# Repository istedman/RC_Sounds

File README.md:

# RC Sounds
A simple, low cost sound effect module for R/C vehicles, land or water based. It utilises a DF Robot DFR0299 MP3 module to continuously play a selected MP3 sound file. A Microchip ATTiny85 provides MP3 control functions, error handling and can support two servo PWM inputs. A set of 4 switches are used to provide easy selection of the desired sound sample. Using one of the PWM inputs, a horn/siren sound can be overlaid and once it finishes playing, normal sound resume. The horn/siren setting is programmable to allow for different receiver outputs.

A PAM8403 Class D amplifier, with EMC fixes is also provided, this allows the system to drive 2x 8 ohm speakers at 2W. Volume control is provided on-board as well as an option to mute the amplifier and finally use an external amplifier, if desired using the pre-amp outputs.

PCB designed to fit into a Hammond 1594B enclosure.

Total cost of all parts, PCB, enclosure and speakers is approximately £30. See the BOM directory for an HTML export with full ordering part numbers.

## Current state as of 25th June 2025.
Design is working well. Has based compatibility tests with multiple AM/2.4 GHz receivers, 2-6 channels and has been field tested.

Use the updated V1.2_1_int software, this adds 4 speeds to the engine sounds and utilises the auxilary input to act as the throttle. The software is written in the Arduino IDE, it uses the ATtinyCore library and no bootloader. The board must be programmed using a progammer, I use a USBASP. To allow the PWM settings function to work, you have to disable the reset function on the fuses. A high voltage programmer is required to unlock. I use this design, https://github.com/wokwi/attiny-hvsp-programmer and clip onto the ATTiny85. All fuse setting defined in the software.

ATTiny85 fuse settings are in the header of the main source code, use USBASP/Avrdudess to set them.

## Boat sound effects SD card image now available

My example SD card image, for boats has now been uploaded to the repository.

## Powering the design

Power is from a 3.7-12V supply or the receiver BEC circuit. Unit has a polyfuse to protect against reverse polarity and a linear regulator.
Do not use with a 1S LiPO ESC or any other ESC that boosts the BEC output. The current design assumes the stndard +5V BEC output voltage. My 1S LiPO ESCs output
6 or 7.2V to boost the servo power, using such an ESC (Trackstar Gen II 120A or Hobbywing Xerun) would irreprably damage the design as it will operate with 5.5V maximum.

You will need an UltraBEC/SuperBEC ESC, i.e. one that can output 2A @ 5V for reliable operation. This unit can demand a peak 0.6A @ 5V, when tested with a 1A BEC, and 3-4 servos, I had a few brownouts. If it reandomly resets at the same time as your receiver, use the external power option and remove the BEC jumper!

## Schematic and circuit description

Power comes from the 5V BEC output of the ESC, if you fit a jumper on J7 of from a 3.7-12V source via J2, using appropriate wire. Connections via J2 have a 1.1A polyfuse and a LD29080-5 5V, 800mA LDO regulator, which provde revers polarity protection.

The ATTiny 85 microcontroller provides the control function. It reads the PWM inputs from two receiver channels, the horn/hooter input connects to pin 5 and the throttle input connects to pin 6. 

Communications to/from the DFR0299 MP3 module are via pins 2 & 3 and use a standard 9600 8N1 serial interface. A USB to TTL adaptor can be connected to the TX output of the ATTiny 85 on pin 2 for debug messages, using J3.

A solitary LED, D1 is used to setup functions and when the horn has been activated.

A set of DIP switches, SW1, set various analogue voltages that determine the sound sample to be played. Limits are defined in the software. A setup switch, S1 is used in the setup routine to set the horn on/off position and the throttle positions.

The DAC output of the DFR0299 is connected, via a dual gang audio potentiometer R17A/B to a PAM8403 audio amplifier. J6 provides a pre-amplifier output.
The DFR0299 DAC outputs, post volume control are AC coupled via C2 and C3. Connector J1 can be used to mute the amplifier. Capacitor C10, a 47uF capacitor, is to reduce the effects of the amplifier on the power supplies. I have added the recommended filter circuit to the output stage, using FB1-FB4 and C12-C15, this reduces radio emissions in the region of 25-40 MHz, important for RC usage as there are still some 27 and 40 MHz systems around.

Into 8 ohm speakers the design can deliver 1.8W. Peak power i've observed has been close to 2W.

A photo of the PCB

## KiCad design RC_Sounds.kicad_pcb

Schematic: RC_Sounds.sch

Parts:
C1, C8, C17: 100nF; C_0603_HandSoldering
C2, C3: 470nF; C_0603_HandSoldering
C4, C16: 10uF; CP_Tantalum_Case-B_EIA-3528-21_Hand
C5, C7: SPO; C_0603_HandSoldering
C6, C9: 1uF; C_0805_HandSoldering
C10: 470uF; CP_Tantalum_Case-E_EIA-7260-38_Hand
C11: 1uF; CP_Tantalum_Case-A_EIA-3216-18_Hand
C12, C13, C15: 220pF; C_0603_HandSoldering
C14: 220pf; C_0603_HandSoldering
D1: LED-GREEN0603; LED-0603
F1: Polyfuse_Small; Fuse_SMD1206_HandSoldering
FB1, FB2, FB3, FB4: Ferrite_Bead_Small; R_0805
H1, H2, H3, H4: STAND-OFFTIGHT; STAND-OFF-TIGHT
J1, J7: CONN_02; 1X02
J2: AVR_SPI_PROG_3X2PTH; 2X3
J3: CONN_03; 1X03
J4: CONN_02; SCREWTERMINAL-3.5MM-2
J5: CONN_04; SCREWTERMINAL-3.5MM-4
J6: CONN_04; 1X04
M1, M2: Motor_Servo_JR; 1X03
R1, R2, R5, R7, R8, R12: 10K; R_0603_HandSoldering
R3, R4: 0; R_0603_HandSoldering
R6: 2.2K; R_0603_HandSoldering
R9: 100K; R_0603_HandSoldering
R10: 47K; R_0603_HandSoldering
R11: 22K; R_0603_HandSoldering
R13: 4.7K; R_0603_HandSoldering
R14, R15: 1K; R_0603_HandSoldering
R16: 470; R_0603_HandSoldering
R17: PTV112
S1: MOMENTARY-SWITCH; TACTILE_SWITCH_SMD_5.2MM
SW1: SW_DIP_x04; DIPSWITCH-04-SMD
U1: LD29080DTR50; TO-252-2
U2: ATtiny85-20SU; SOIC-8-N
U3: PAM8403DR; SO-16-N
U4: DFR0299; MODULE_DFR0299

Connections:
+5V: C4.1, C8.1, C9.1, C10.1, C11.1, C16.1, C17.1, J2.2, J7.1, R5.1, R7.1, R8.1, R16.2, U1.3 (VO), U2.8, U3.4, U3.6, U3.13, U4.1
/LEFT+: C15.1, FB3.2, J5.1
/LEFT-: C14.1, FB1.2, J5.2
/L_AUDIO: C2.1, J6.1, R17.2.2
/RIGHT+: C12.1, FB2.2, J5.4
/RIGHT-: C13.1, FB4.2, J5.3
/RX_MICRO: J3.2, R15.1, U2.3
/R_AUDIO: C3.1, J6.4, R17.1.2
/SW_RX: R14.1, U4.2
/SW_TX: R15.2, U4.3
/TX_MICRO: J3.3, R14.2, U2.2
GND: C1.2, C4.2, C5.2, C6.2, C7.2, C8.2, C9.2, C10.2, C11.2, C12.2, C13.2, C14.2, C15.2, C16.2, C17.2, J1.1, J2.6, J3.1, J4.1, J6.2, J6.3, M1.3 (-), M2.3 (-), R9.2, R17.1.1, R17.2.1, S1.1, SW1.1, SW1.2, SW1.3, SW1.4, U1.2 (GND), U2.4, U3.2, U3.11, U3.15, U4.7, U4.10
unnamed: C1.1, F1.2, U1.1 (VI)
unnamed: C2.2, R1.1
unnamed: C3.2, R2.1
unnamed: C5.1, J2.4, R3.1, U2.5
unnamed: C6.1, U3.8
unnamed: C7.1, J2.1, R4.1, U2.6
unnamed: D1.A, R16.1
unnamed: D1.C, J2.3, U2.7
unnamed: F1.1, J4.2
unnamed: FB1.1, U3.3
unnamed: FB2.1, U3.16
unnamed: FB3.1, U3.1
unnamed: FB4.1, U3.14
unnamed: J1.2, R7.2, U3.12
unnamed: J2.5, R6.1, R8.2, R9.1, R10.1, R11.1, R12.1, R13.1, U2.1
unnamed: J7.2, M1.2 (+)
unnamed: M1.1 (PWM), R3.2
unnamed: M2.1 (PWM), R4.2
unnamed: R1.2, U3.7
unnamed: R2.2, U3.10
unnamed: R5.2, U3.5
unnamed: R6.2, S1.3
unnamed: R10.2, SW1.8
unnamed: R11.2, SW1.7
unnamed: R12.2, SW1.6
unnamed: R13.2, SW1.5
unnamed: R17.1.3, U4.4
unnamed: R17.2.3, U4.5

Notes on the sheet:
Fit to disable PAM8403 amplifier.
EMC filtering of class D output
Non-amplified output for external Amp
PB5 Analogue in/switch PB2 LED PB1 (horn) PB0 (Aux in for horn)
Setup switch
Horn/hooter input
Optional speed/aux input
J7 allows receiver BEC output to power the circuit
Serial debug
Missing on V1.1 PCB

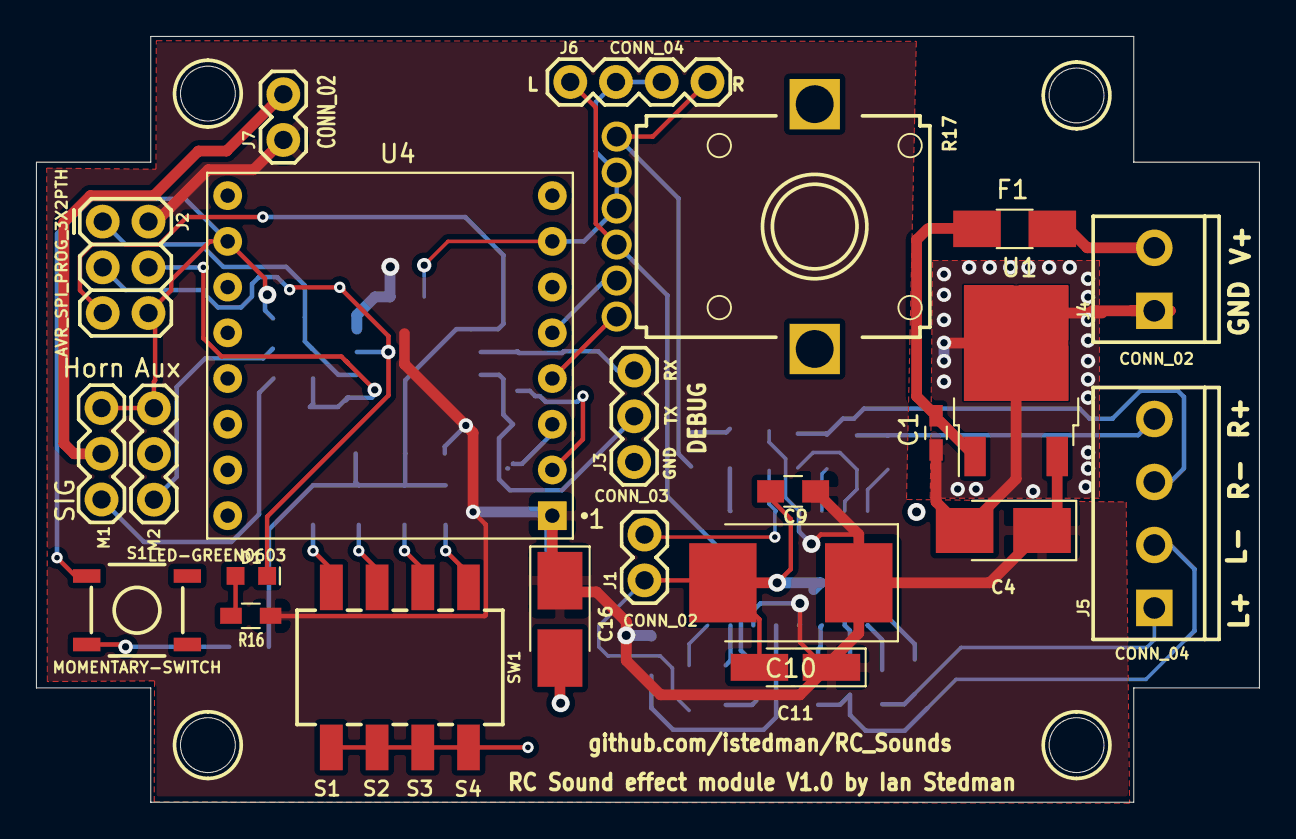
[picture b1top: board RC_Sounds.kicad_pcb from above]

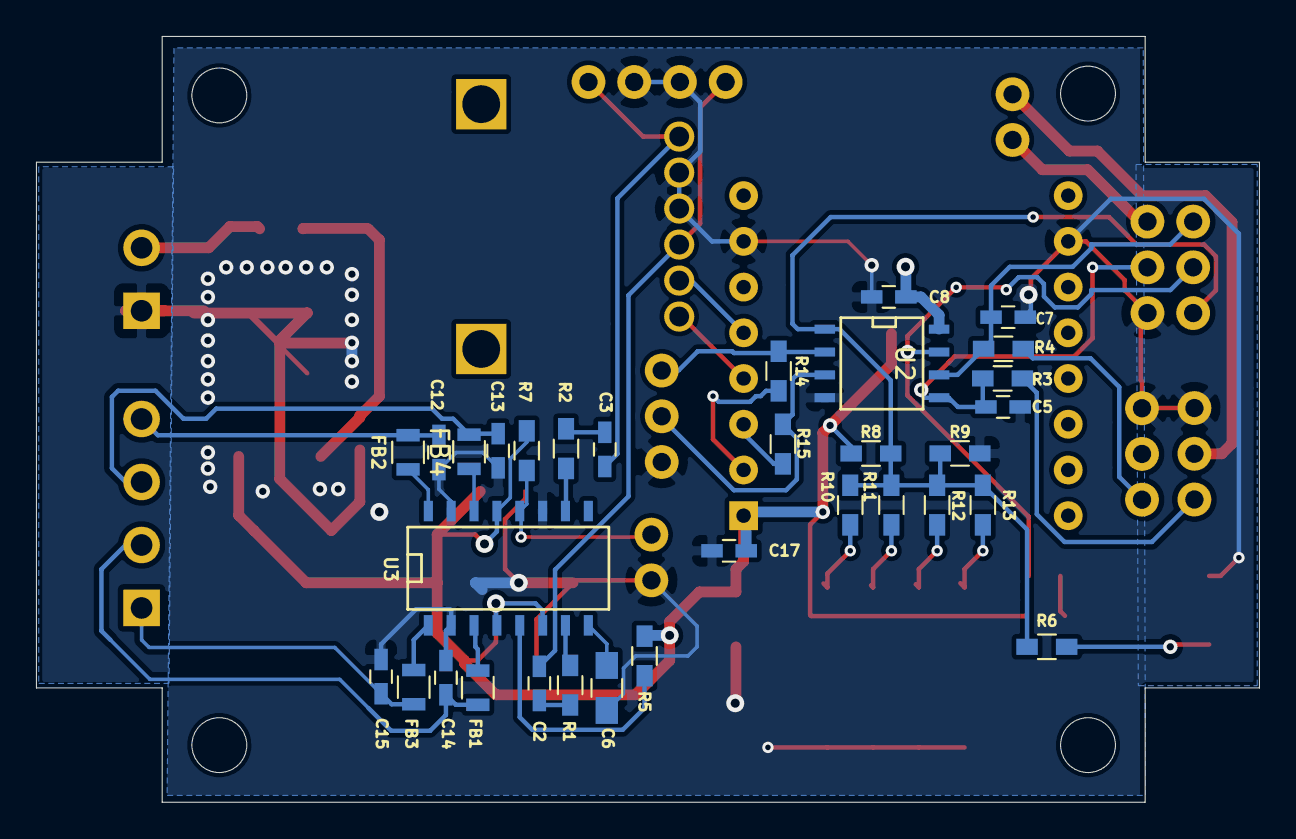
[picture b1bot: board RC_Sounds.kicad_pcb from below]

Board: 2 copper layers, 67.9 x 42.5 mm, 59 parts (32 on the bottom side), 40 nets.

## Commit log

2021-06-12 Add files via upload
    Updated software, now with support for 4 speeds. It will change the speed of the engine sound/
2021-06-12 Add files via upload
    Corrected error in analogue input connection in schematic and PCB.
2021-06-12 Add files via upload
    Corrected error in analogue input
2021-06-12 Add files via upload
    My current SD Card image. Files came from, https://sound-effects.bbcrewind.co.uk/ & https://freesound.org/. Horn sound mixed using my normal process.
2022-06-05 Add files via upload
    This fixes multiple issues:
    1) If the unit was externally powered (not via BEC), there was no horn input and it looked for <VALUE to operate, the horn would continually sound.
    2) The gear change was like a dodgy automatic, going up/down around the trigger points. Moving average filter + hysteresis fixed this.
    3) Sometimes the 'advert' used to play the horn, was cut off, added new code to fix this, now using a 13 second delay. Will improve in next release.
    4) Reduced the loop time from ~250ms to 32ms, this helped the averaging filter respond quicker and is more efficient. The Pulsein() function is a paint.
2022-06-07 Update README.md
    Added notes on powering the design.
2025-06-25 Add files via upload
    Software changed to use integer rather than floating point, flash memory usages drops from 97% to 88%, leaving room for expansion
